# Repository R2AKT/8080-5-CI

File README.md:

License addendum - https://github.com/R2AKT/8080-5-CI/blob/main/Addendum.txt

# 8080-5-CI

Debug and download module. To connect to the debugging board - https://github.com/R2AKT/Stepper.

The control is carried out from the graphical interface - https://github.com/R2AKT/8080-5-CI-App.

Модуль отладки и загрузки. Для подключения к плате отладки - https://github.com/R2AKT/Stepper.

Управление осуществляется из графической оболочки - https://github.com/R2AKT/8080-5-CI-App.

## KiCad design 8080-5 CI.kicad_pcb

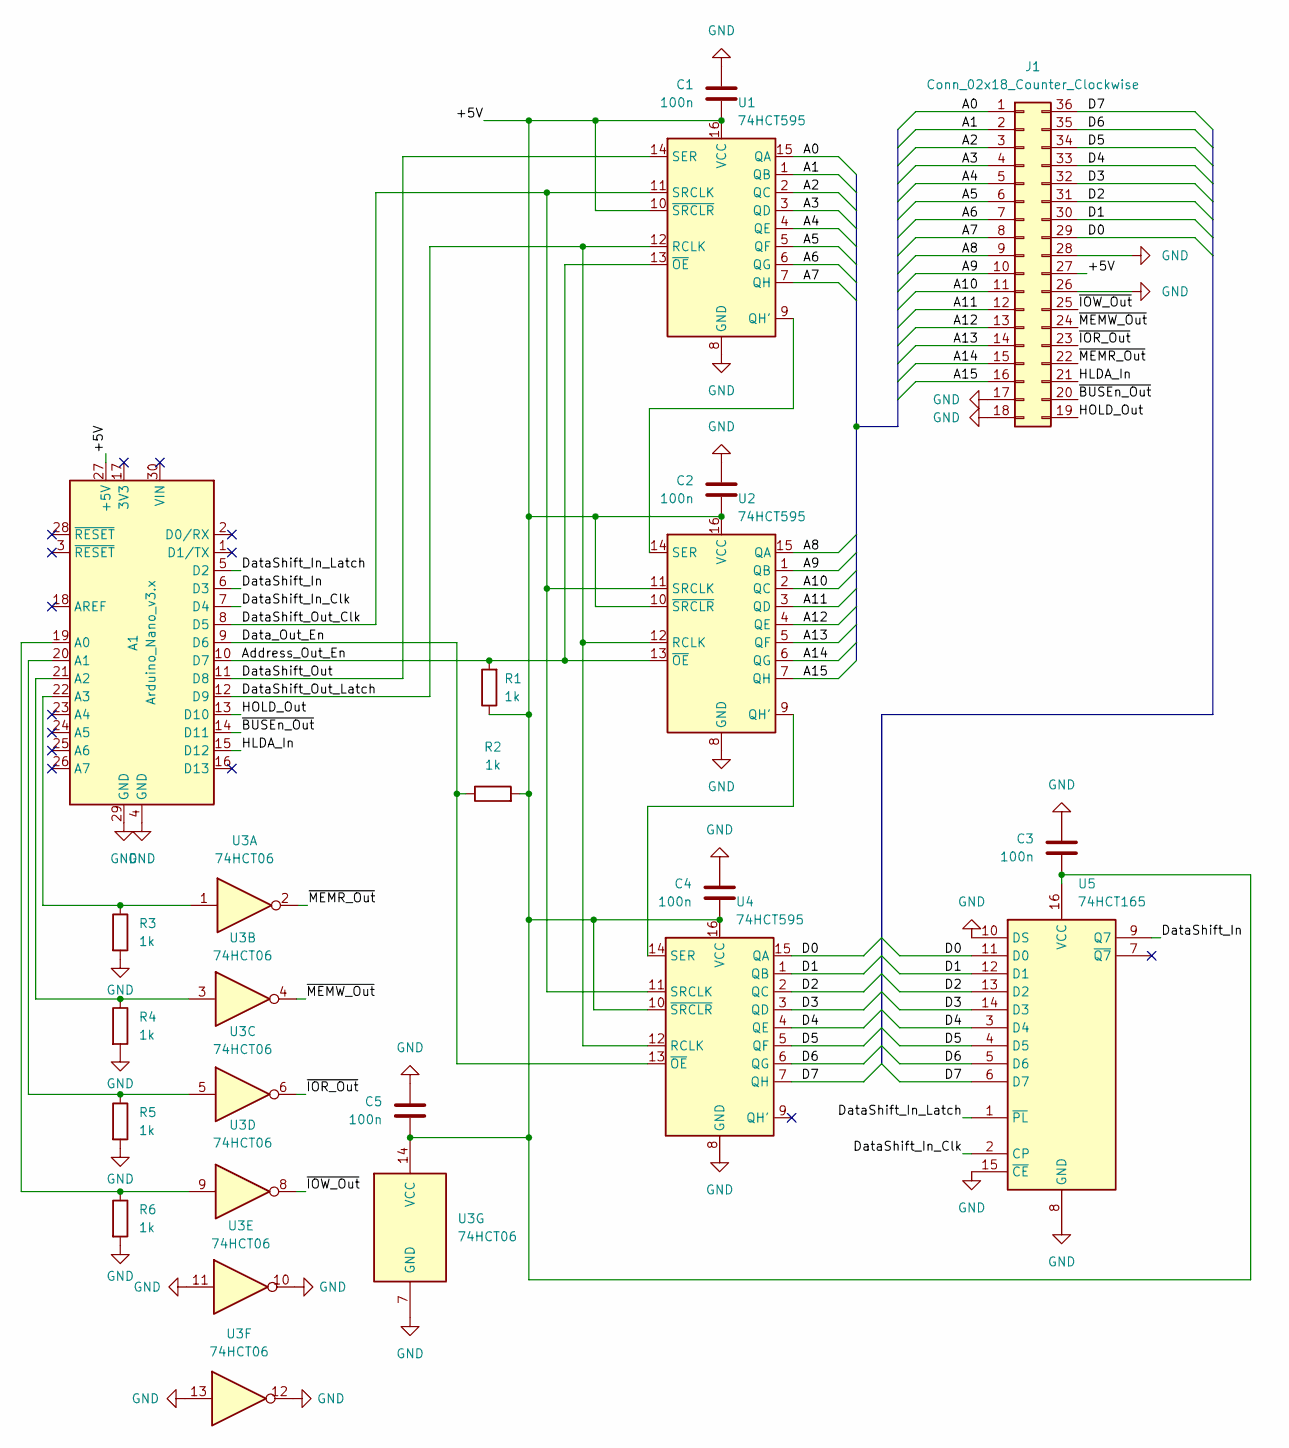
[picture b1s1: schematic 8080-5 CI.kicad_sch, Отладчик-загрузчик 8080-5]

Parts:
A1: Arduino_Nano_v3.x; Arduino_Nano
C1, C2, C3, C4, C5: 100n; C_0805_2012Metric_Pad1.18x1.45mm_HandSolder
J1: Conn_02x18_Counter_Clockwise; PinHeader_2x18_P2.54mm_Horizontal
R1, R2, R3, R4, R5, R6: 1k; R_0805_2012Metric_Pad1.20x1.40mm_HandSolder
U1, U2, U4: 74HCT595; DIP-16_W7.62mm_LongPads
U3: 74HCT06; DIP-14_W7.62mm_LongPads
U5: 74HCT165; DIP-16_W7.62mm_LongPads

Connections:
/+5V: A1.27 (+5V), C1.2, C2.2, C3.2, C4.2, C5.2, J1.27, R1.1, R2.2, U1.10 (~SRCLR), U1.16 (VCC), U2.10 (~SRCLR), U2.16 (VCC), U3.14 (VCC), U4.10 (~SRCLR), U4.16 (VCC), U5.16 (VCC)
/A0: J1.1, U1.15 (QA)
/A1: J1.2, U1.1 (QB)
/A2: J1.3, U1.2 (QC)
/A3: J1.4, U1.3 (QD)
/A4: J1.5, U1.4 (QE)
/A5: J1.6, U1.5 (QF)
/A6: J1.7, U1.6 (QG)
/A7: J1.8, U1.7 (QH)
/A8: J1.9, U2.15 (QA)
/A9: J1.10, U2.1 (QB)
/A10: J1.11, U2.2 (QC)
/A11: J1.12, U2.3 (QD)
/A12: J1.13, U2.4 (QE)
/A13: J1.14, U2.5 (QF)
/A14: J1.15, U2.6 (QG)
/A15: J1.16, U2.7 (QH)
/Address_Out_En: A1.10 (D7), R1.2, U1.13 (~OE), U2.13 (~OE)
/D0: J1.29, U4.15 (QA), U5.11 (D0)
/D1: J1.30, U4.1 (QB), U5.12 (D1)
/D2: J1.31, U4.2 (QC), U5.13 (D2)
/D3: J1.32, U4.3 (QD), U5.14 (D3)
/D4: J1.33, U4.4 (QE), U5.3 (D4)
/D5: J1.34, U4.5 (QF), U5.4 (D5)
/D6: J1.35, U4.6 (QG), U5.5 (D6)
/D7: J1.36, U4.7 (QH), U5.6 (D7)
/DataShift_In: A1.6 (D3), U5.9 (Q7)
/DataShift_In_Clk: A1.7 (D4), U5.2 (CP)
/DataShift_In_Latch: A1.5 (D2), U5.1 (~PL)
/DataShift_Out: A1.11 (D8), U1.14 (SER)
/DataShift_Out_Clk: A1.8 (D5), U1.11 (SRCLK), U2.11 (SRCLK), U4.11 (SRCLK)
/DataShift_Out_Latch: A1.12 (D9), U1.12 (RCLK), U2.12 (RCLK), U4.12 (RCLK)
/Data_Out_En: A1.9 (D6), R2.1, U4.13 (~OE)
/HLDA_In: A1.15 (D12), J1.21
/HOLD_Out: A1.13 (D10), J1.19
/~BUSEn_Out: A1.14 (D11), J1.20
/~IOR_Out: J1.23, U3.6
/~IOW_Out: J1.25, U3.8
/~MEMR_Out: J1.22, U3.2
/~MEMW_Out: J1.24, U3.4
GND: A1.4 (GND), A1.29 (GND), C1.1, C2.1, C3.1, C4.1, C5.1, J1.17, J1.18, J1.26, J1.28, R3.2, R4.2, R5.2, R6.2, U1.8 (GND), U2.8 (GND), U3.7 (GND), U3.10, U3.11, U3.12, U3.13, U4.8 (GND), U5.8 (GND), U5.10 (DS), U5.15 (~CE)
unnamed: A1.19 (A0), R6.1, U3.9
unnamed: A1.20 (A1), R5.1, U3.5
unnamed: A1.21 (A2), R4.1, U3.3
unnamed: A1.22 (A3), R3.1, U3.1
unnamed: U1.9 (QH'), U2.14 (SER)
unnamed: U2.9 (QH'), U4.14 (SER)

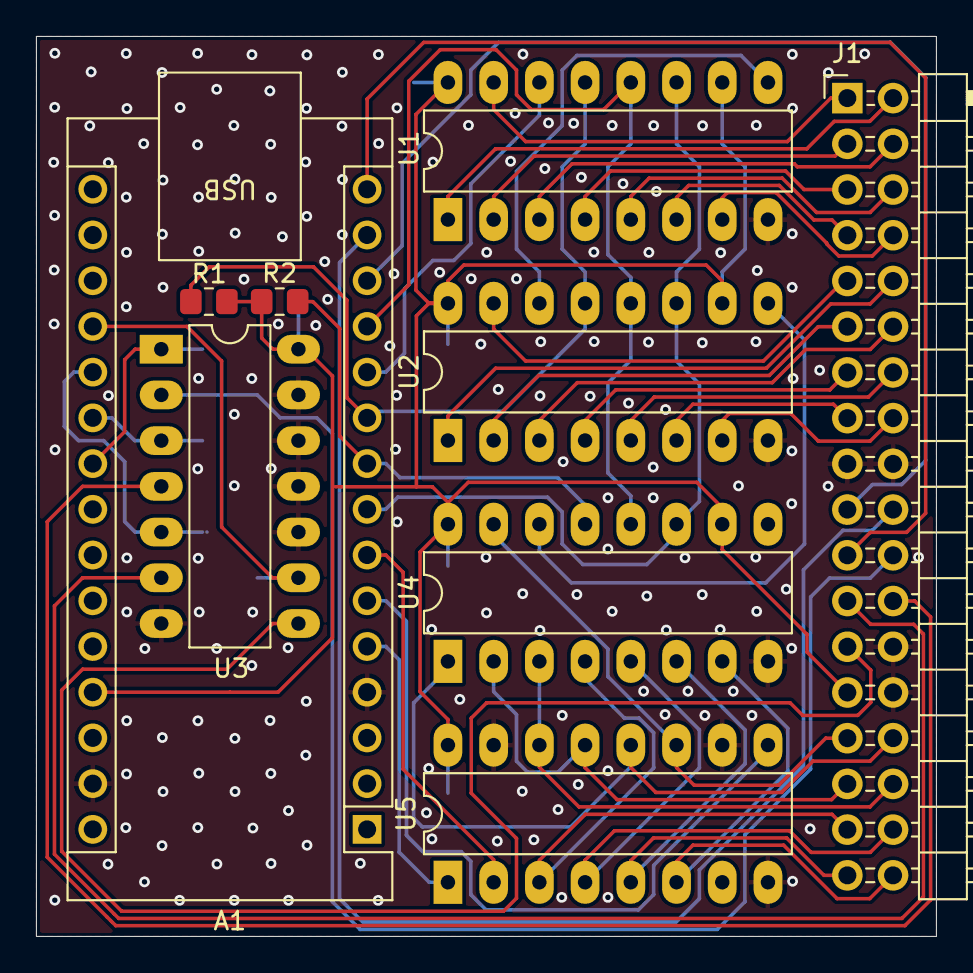
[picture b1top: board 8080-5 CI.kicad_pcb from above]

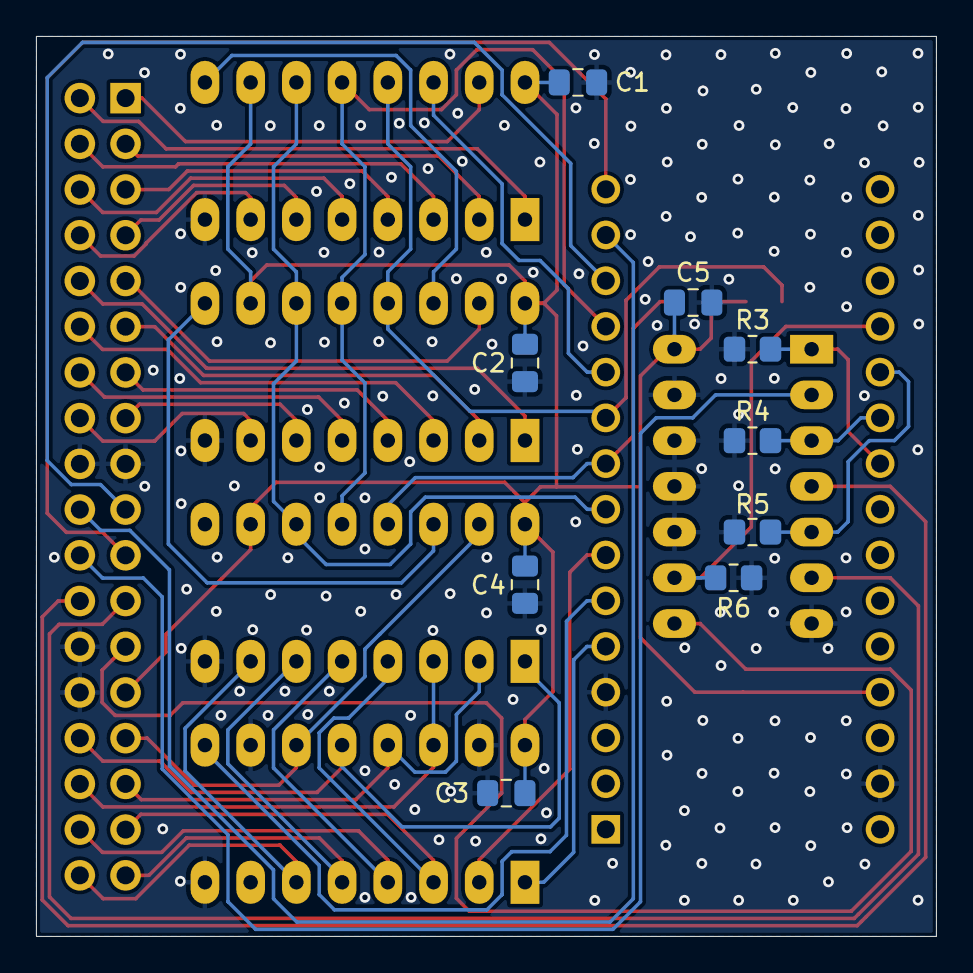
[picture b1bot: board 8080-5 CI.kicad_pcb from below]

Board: 2 copper layers, 50.0 x 50.0 mm, 18 parts (9 on the bottom side), 47 nets.

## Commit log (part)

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2026-02-16 Add Arduino firmware (test version), fix schematic

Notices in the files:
README.md:
License: MIT
